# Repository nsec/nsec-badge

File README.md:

NorthSec 2025 badge
===================

Brought to you by the Team badge of NorthSec.

## Overview

<p align="center">
   <br>
</p>

## Hardware

The NorthSec 2025 badge is loosely based on the ESP32-C3 design with an
[ESP32-C3 microcontroller](https://www.espressif.com/en/products/socs/esp32-c3)
(ESP32-C3-WROOM-02-N4) which is used to drive several periphery devices:

- Eighteen [NeoPixel](https://en.wikipedia.org/wiki/Adafruit_Industries#NeoPixel) RGB LEDs
- Five buttons
- One IR 'pairing' connector
- Two [Shitty Add-On V1.69bis](https://hackaday.com/2019/03/20/introducing-the-shitty-add-on-v1-69bis-standard/) connector

The badge is powered through a USB-C port or through 3 AAA batteries.

If you wish to hack your badge or create a new one based on the hardware. All
the information [is available here](hw/2025/).

## Building the firmware

The firmware is based on the [Espressif IoT Development
Framework](https://docs.platformio.org/en/latest/frameworks/espidf.html). The
build system uses
[PlatformIO](https://docs.platformio.org/en/stable/what-is-platformio.html) to
easily manage the dependencies.

You can install it on Debian / Ubuntu in a python virtualenv with these
commands:

```bash
sudo apt install python3-virtualenv

virtualenv .venv
. .venv/bin/activate

pip install platformio
```

The installation procedure for your OS may differ a little, please consult the
[PlatformIO
documentation](https://docs.platformio.org/en/stable/core/installation/index.html)
if you have any difficulties.

Once the installation is complete you can build the firmware:

```bash
# Conference firmware
pio run -e conference

# CTF firmware
pio run -e ctf
```

## Flashing

Flash the firmware with this command:

```bash
# Conference firmware
pio run -t upload -e conference

# CTF firmware
pio run -t upload -e ctf
```

If multiple badges are connected, you can select which badge will be flash with
the `--upload-port <port_name>` option:

```bash
# Conference firmware
pio run -t upload -e conference --upload-port <port_name>
```

To improve the upload speed, you can skip the build validation/process with the
`-t nobuild` option:

```bash
# Conference firmware
pio run -t upload -t nobuild -e conference
```

## Debugging

To read the logging statements output on the USB serial interface, it is
possible to use `pio device monitor` or `idf.py`'s `monitor` command.

However, you can use your preferred terminal emulator by pointing it to the
`/dev/ttyACM0` device. The badge is configured to output at `115200` bauds,
without parity, and with one stop bit per character.

Note that electrically resetting the board using the hardware switch will cause
the pseudo-terminal device to disappear, making it hard to read the logs
emitted during boot.

Pulsing the DTR signal (lowering it for 1 second) will cause the board to reset
without affecting the pseudo-terminal device, allowing you to read early-boot
messages. This is supported by most terminal emulators.

## Credits
NorthSec CTF badge 2025 is brought to you by the teamwork of:

 - [abdelq](https://github.com/abdelq)
 - [IterateMe](https://github.com/IterateMe)
 - [lle](https://github.com/lle)
 - [nyx0](https://github.com/nyx0)
 - [p0ns](https://github.com/p0ns)
 - [padraignix](https://github.com/padraignix)
 - [Svieg](https://github.com/Svieg)
 - [sylemieux](https://github.com/sylemieux)
 - [TheKGBSpy](https://github.com/TheKGBSpy)
 - [mjeanson](https://github.com/mjeanson)

Special thanks to:
 - [20th](https://github.com/20th)
 - [jgalar](https://github.com/jgalar)

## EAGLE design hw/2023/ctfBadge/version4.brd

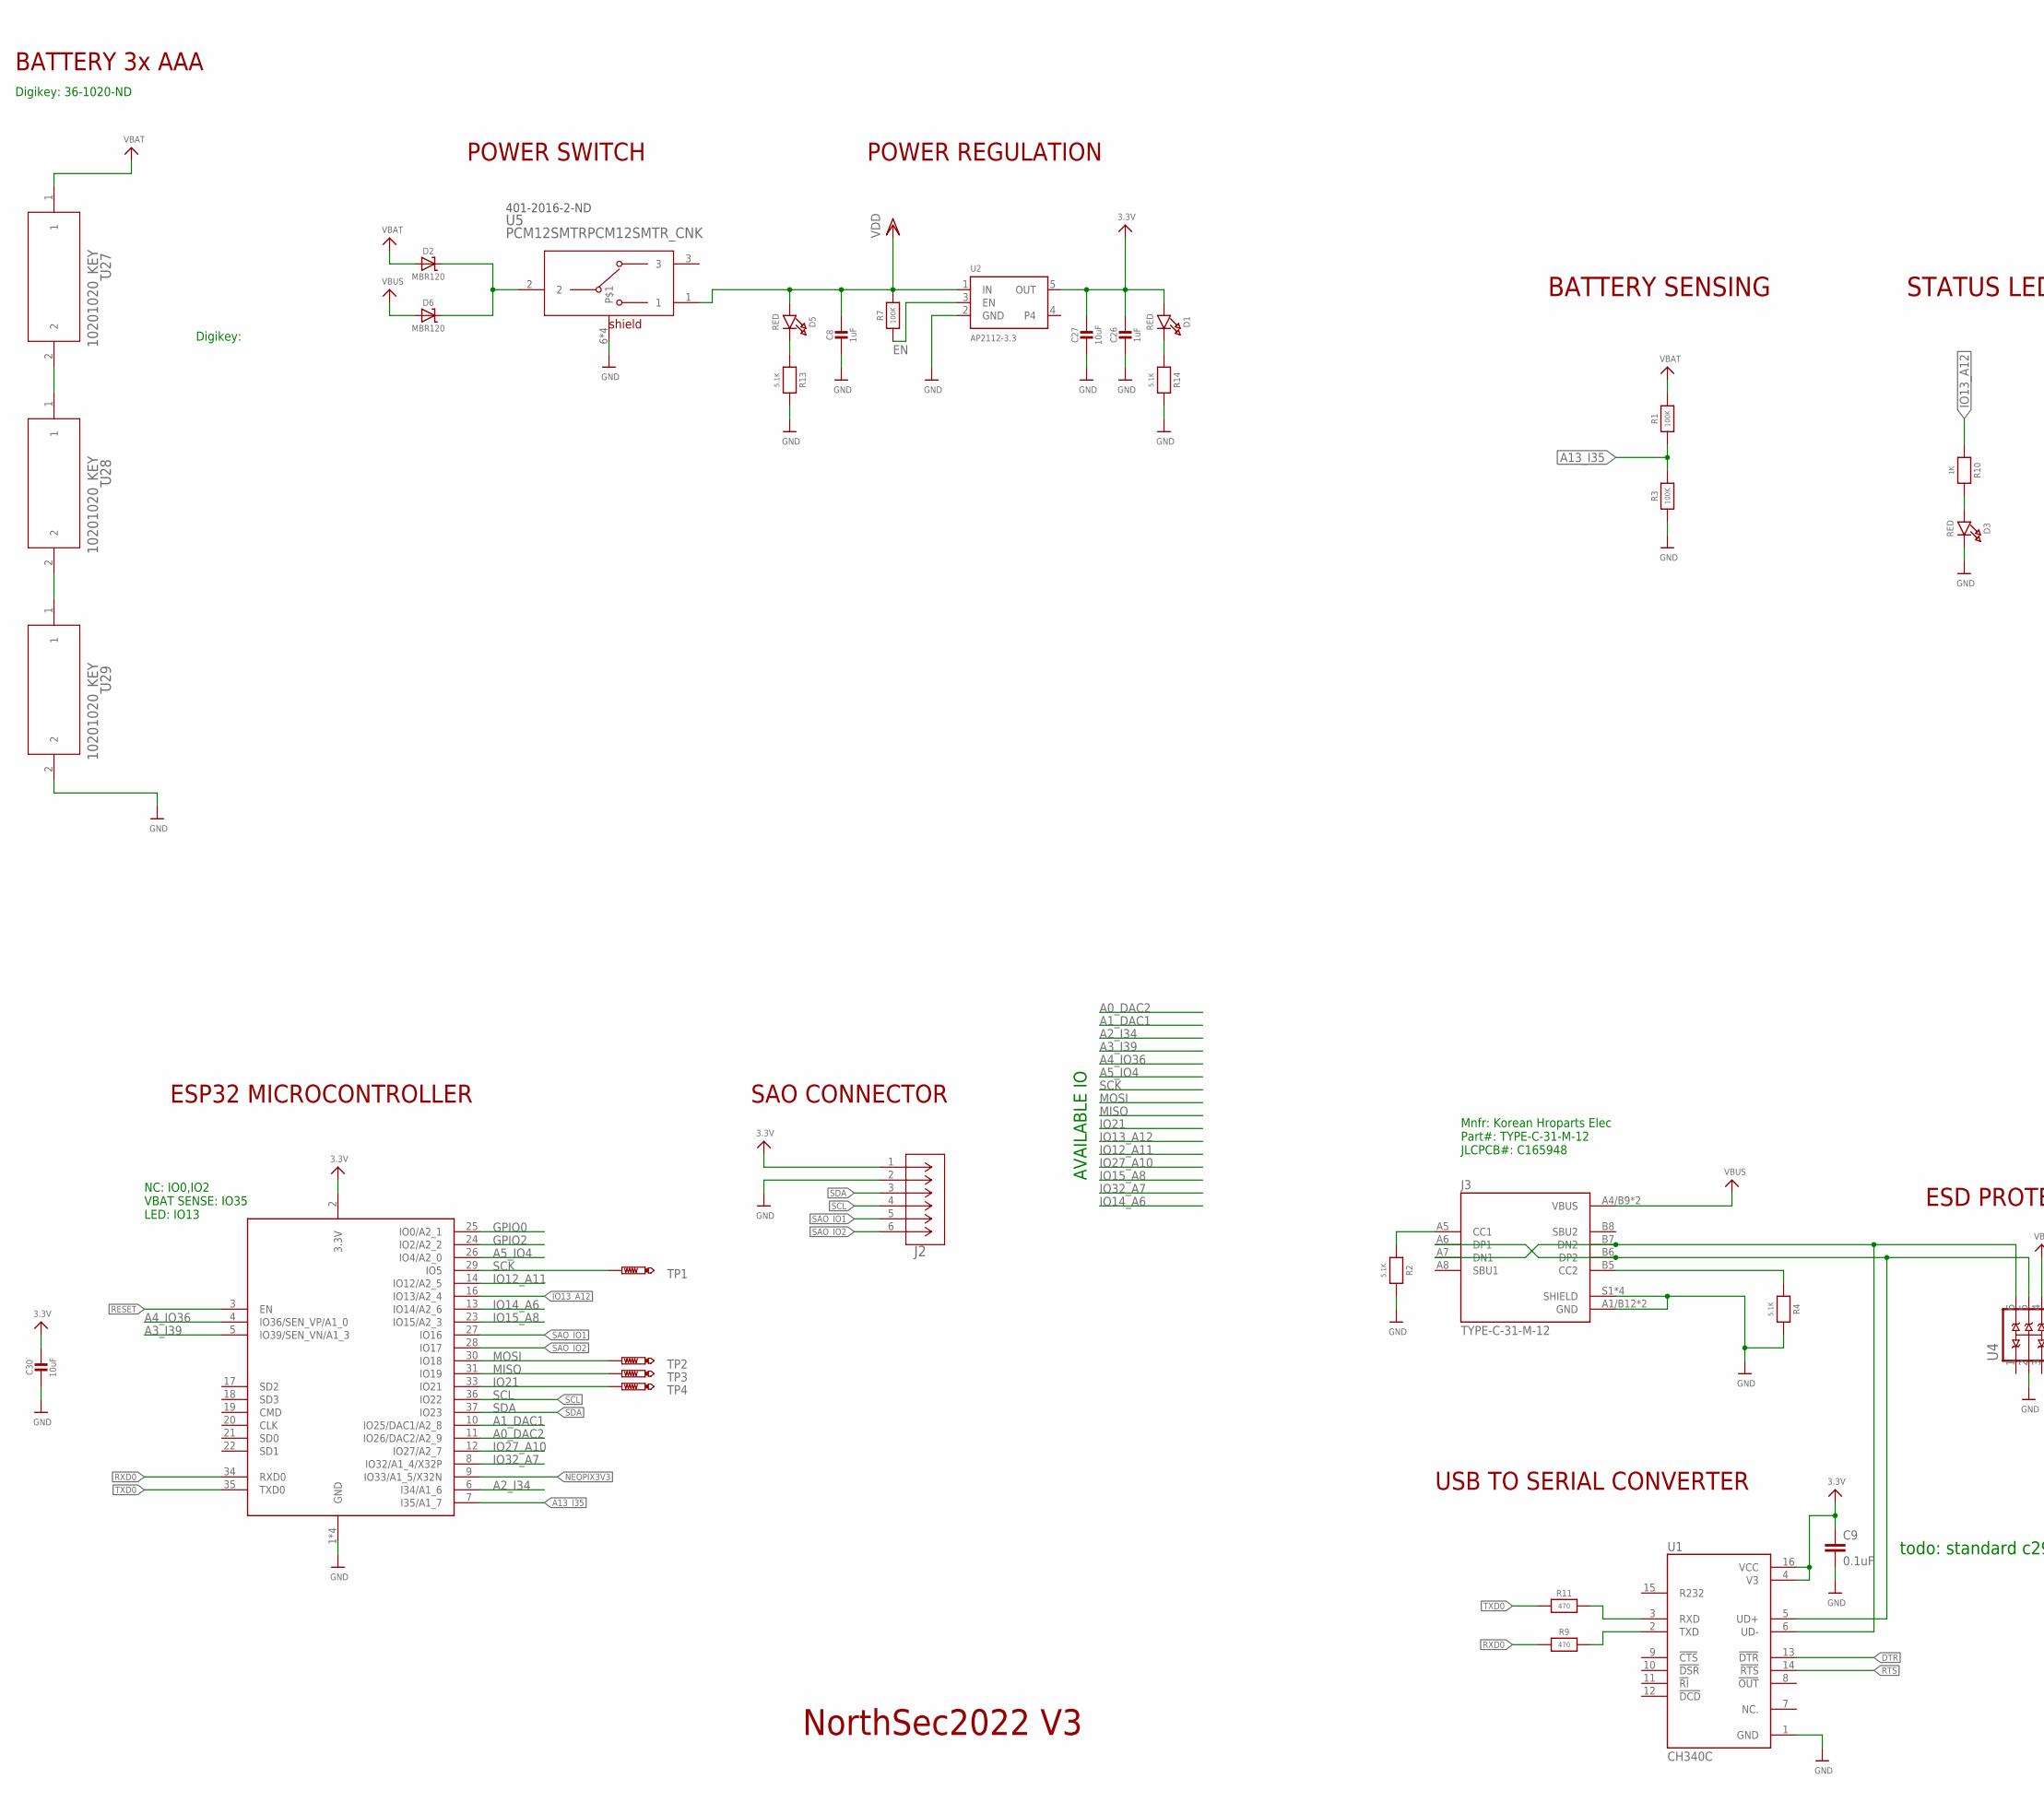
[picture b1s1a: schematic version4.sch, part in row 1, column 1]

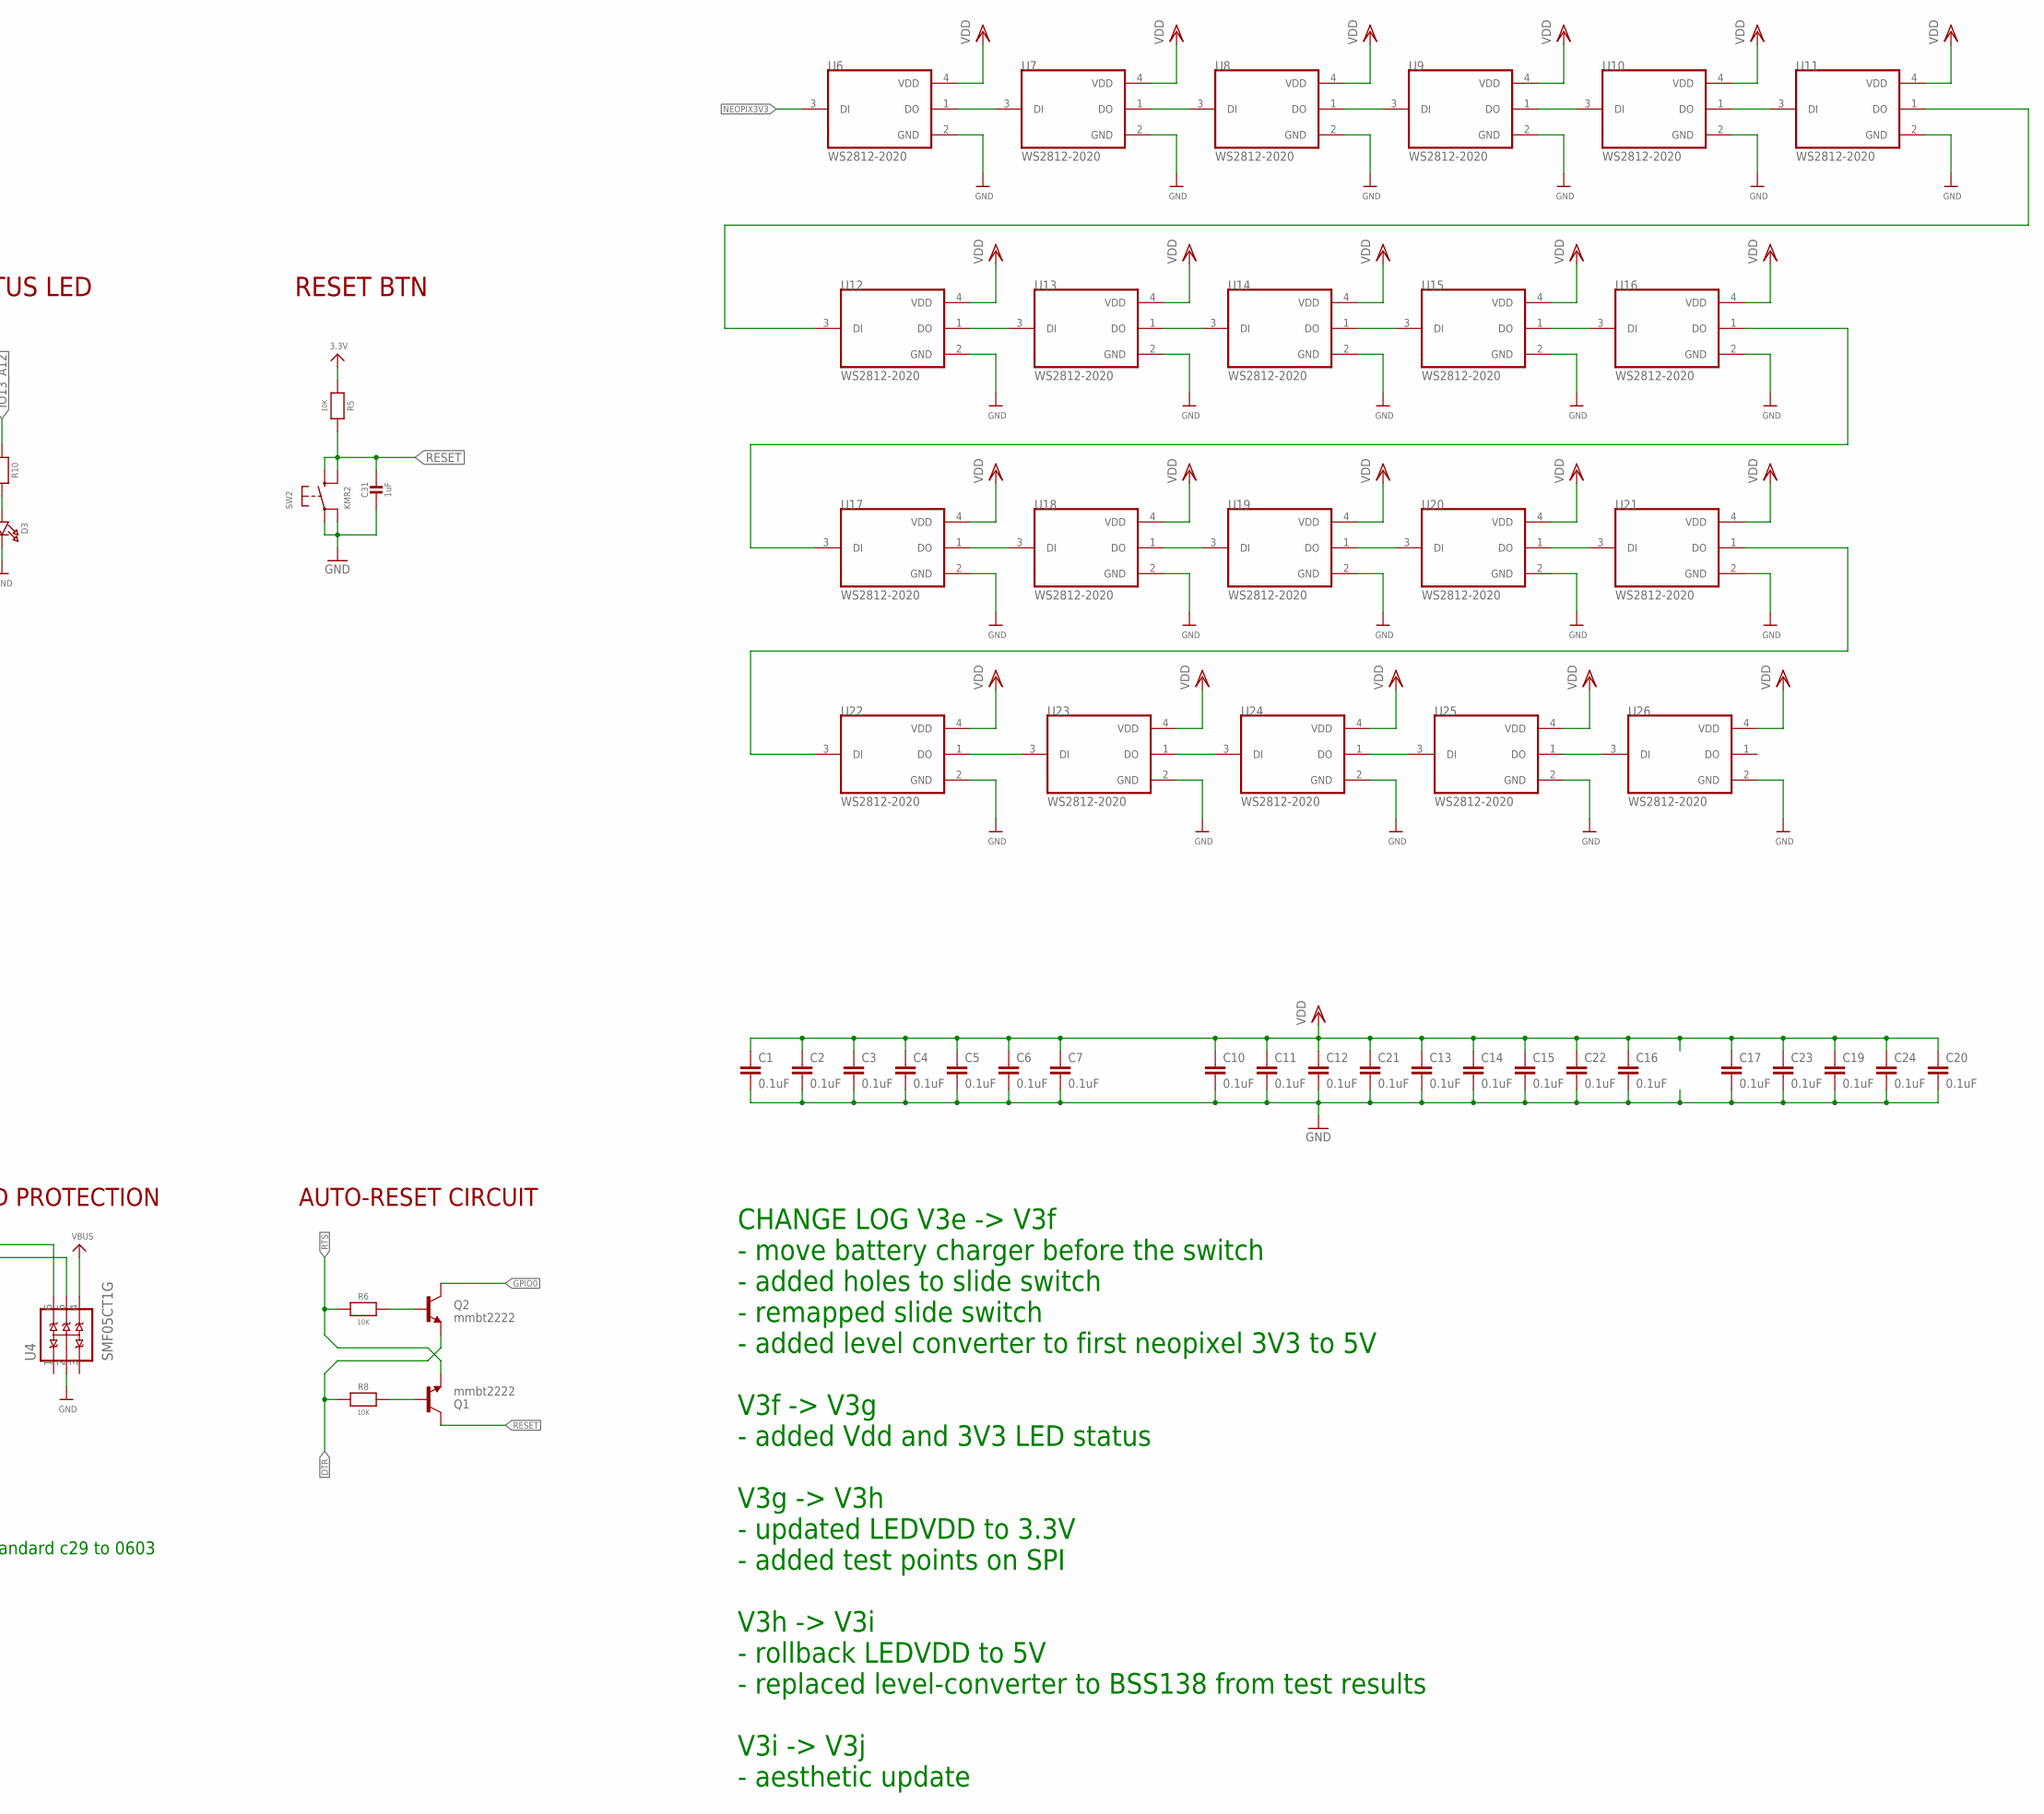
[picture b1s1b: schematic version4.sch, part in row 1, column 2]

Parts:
C1, C2, C3, C4, C5, C6, C7, C9, C10, C11, C12, C13, C14, C15, C16, C17, C19, C20, C21, C22, C23, C24: 0.1uF; C0603
C8, C26, C31: 1uF; 0603-NO
C27, C30: 10uF; 0805-NO
D1, D3, D5: RED; CHIPLED_0805_NOOUTLINE
D2, D6: MBR120; SOD-123
J2: SSW-103-22-F-D-VS-K-TRCON3_SSW-D-DUMZ_HDR_SAI; CON3_SSW-D-DUMZ_HDR_SAI
J3: TYPE-C-31-M-12; HRO_TYPE-C-31-M-12
Q1, Q2: mmbt2222; SOT23-3
R1, R3, R7: 100K; 0603-NO
R2, R4, R13, R14: 5.1K; 0603-NO
R5, R6, R8: 10K; 0603-NO
R9, R11: 470; 0603-NO
R10: 1K; 0603-NO
SW2: KMR2; BTN_KMR2_4.6X2.8
TP1, TP2, TP3, TP4: PTR1B1,27; B1,27
U1: CH340C; SOIC127P600X180-16N
U2: AP2112-3.3; SOT23-5
U4: SMF05CT1G; SOT65P210X110-6N
U5: PCM12SMTRPCM12SMTR_CNK; PCM12SMTR_CNK
U6, U7, U8, U9, U10, U11, U12, U13, U14, U15, U16, U17, U18, U19, U20, U21, U22, U23, U24, U25, U26: WS2812-2020; LED_WS2812-2020
U27, U28, U29: 10201020_KEY; 1020_KEY
X2: ESP32_WROOM32_SKINNY; WROOM32_SKINNY

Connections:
3.3V: C9.1, C26.1, C27.1, C30.1, D1.A, J2.1, R5.1, U1.4 (V3), U1.16 (VCC), U2.5 (OUT), X2.2 (3.3V)
A0_DAC2: X2.11 (IO26/DAC2/A2_9)
A1_DAC1: X2.10 (IO25/DAC1/A2_8)
A2_I34: X2.6 (I34/A1_6)
A3_I39: X2.5 (IO39/SEN_VN/A1_3)
A4_IO36: X2.4 (IO36/SEN_VP/A1_0)
A5_IO4: X2.26 (IO4/A2_0)
A13_I35: R1.1, R3.2, X2.7 (I35/A1_7)
DTR: Q2.2 (E), R8.1, U1.13 (!DTR)
EN: R7.1, U2.3 (EN)
GND: C1.2, C2.2, C3.2, C4.2, C5.2, C6.2, C7.2, C8.2, C9.2, C10.2, C11.2, C12.2, C13.2, C14.2, C15.2, C16.2, C17.2, C19.2, C20.2, C21.2, C22.2, C23.2, C24.2, C26.2, C27.2, C30.2, C31.2, D3.C, J2.2, J3.A1/B12 (GND), J3.B1/A12 (GND), J3.S1 (SHIELD), J3.S2 (SHIELD), J3.S3 (SHIELD), J3.S4 (SHIELD), R2.2, R3.1, R4.2, R13.2, R14.2, SW2.A, SW2.A' (P1), U1.1 (GND), U2.2 (GND), U4.2 (A), U5.6, U5.7, U5.8, U5.9, U6.2 (GND), U7.2 (GND), U8.2 (GND), U9.2 (GND), U10.2 (GND), U11.2 (GND), U12.2 (GND), U13.2 (GND), U14.2 (GND), U15.2 (GND), U16.2 (GND), U17.2 (GND), U18.2 (GND), U19.2 (GND), U20.2 (GND), U21.2 (GND), U22.2 (GND), U23.2 (GND), U24.2 (GND), U25.2 (GND), U26.2 (GND), U29.2, X2.1 (GND), X2.15 (GND), X2.38 (GND), X2.P$1 (GND)
GPIO0: Q2.3 (C), X2.25 (IO0/A2_1)
GPIO2: X2.24 (IO2/A2_2)
IO12_A11: X2.14 (IO12/A2_5)
IO13_A12: R10.1, X2.16 (IO13/A2_4)
IO14_A6: X2.13 (IO14/A2_6)
IO15_A8: X2.23 (IO15/A2_3)
IO21: TP4.TP, X2.33 (IO21)
IO27_A10: X2.12 (IO27/A2_7)
IO32_A7: X2.8 (IO32/A1_4/X32P)
MISO: TP3.TP, X2.31 (IO19)
MOSI: TP2.TP, X2.30 (IO18)
unnamed: U7.1 (DO), U8.3 (DI)
unnamed: U8.1 (DO), U9.3 (DI)
unnamed: U23.1 (DO), U24.3 (DI)
unnamed: U24.1 (DO), U25.3 (DI)
unnamed: U25.1 (DO), U26.3 (DI)
unnamed: J3.B5 (CC2), R4.1
unnamed: D2.C, D6.C, U5.2
unnamed: J3.A5 (CC1), R2.1
unnamed: U22.1 (DO), U23.3 (DI)
unnamed: U28.2, U29.1
unnamed: U27.2, U28.1
unnamed: R9.2, U1.2 (TXD)
unnamed: J3.A6 (DP1), J3.B6 (DP2), U1.5 (UD+), U4.5 (C4)
unnamed: J3.A7 (DN1), J3.B7 (DN2), U1.6 (UD-), U4.6 (C5)
unnamed: Q1.1 (B), R8.2
unnamed: Q2.1 (B), R6.2
unnamed: R11.2, U1.3 (RXD)
unnamed: D3.A, R10.2
unnamed: D5.C, R13.1
unnamed: D1.C, R14.1
unnamed: U6.1 (DO), U7.3 (DI)
unnamed: U9.1 (DO), U10.3 (DI)
unnamed: U10.1 (DO), U11.3 (DI)
unnamed: U11.1 (DO), U12.3 (DI)
unnamed: U12.1 (DO), U13.3 (DI)
unnamed: U13.1 (DO), U14.3 (DI)
unnamed: U14.1 (DO), U15.3 (DI)
unnamed: U15.1 (DO), U16.3 (DI)
unnamed: U16.1 (DO), U17.3 (DI)
unnamed: U17.1 (DO), U18.3 (DI)
unnamed: U18.1 (DO), U19.3 (DI)
unnamed: U19.1 (DO), U20.3 (DI)
unnamed: U20.1 (DO), U21.3 (DI)
unnamed: U21.1 (DO), U22.3 (DI)
NEOPIX3V3: U6.3 (DI), X2.9 (IO33/A1_5/X32N)
RESET: C31.1, Q1.3 (C), R5.2, SW2.B (S), SW2.B' (S1), X2.3 (EN)
RTS: Q1.2 (E), R6.1, U1.14 (!RTS)
RXD0: R9.1, X2.34 (RXD0)
SAO_IO1: J2.5, X2.27 (IO16)
SAO_IO2: J2.6, X2.28 (IO17)
SCK: TP1.TP, X2.29 (IO5)
SCL: J2.4, X2.36 (IO22)
SDA: J2.3, X2.37 (IO23)
TXD0: R11.1, X2.35 (TXD0)
VBAT: D2.A, R1.2, U27.1
VBUS: D6.A, J3.A4/B9 (VBUS), J3.B4/A9 (VBUS), U4.4 (C3)
VDD: C1.1, C2.1, C3.1, C4.1, C5.1, C6.1, C7.1, C8.1, C10.1, C11.1, C12.1, C13.1, C14.1, C15.1, C16.1, C17.1, C19.1, C20.1, C21.1, C22.1, C23.1, C24.1, D5.A, R7.2, U2.1 (IN), U5.1, U6.4 (VDD), U7.4 (VDD), U8.4 (VDD), U9.4 (VDD), U10.4 (VDD), U11.4 (VDD), U12.4 (VDD), U13.4 (VDD), U14.4 (VDD), U15.4 (VDD), U16.4 (VDD), U17.4 (VDD), U18.4 (VDD), U19.4 (VDD), U20.4 (VDD), U21.4 (VDD), U22.4 (VDD), U23.4 (VDD), U24.4 (VDD), U25.4 (VDD), U26.4 (VDD)

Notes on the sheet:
POWER REGULATION
RESET BTN
USB TO SERIAL CONVERTER
ESP32 MICROCONTROLLER
NC: IO0,IO2 VBAT SENSE: IO35 LED: IO13
BATTERY SENSING
STATUS LED
ESD PROTECTION
AUTO-RESET CIRCUIT
AVAILABLE IO
401-2016-2-ND
CHANGE LOG V3e -> V3f - move battery charger before the switch - added holes to slide switch - remapped slide switch - added level converter to first neopixel 3V3 to 5V V3f -> V3g - added Vdd and 3V3 LED status V3g -> V3h - updated LEDVDD to 3.3V - added test points on SPI V3h -> V3i - rollback LED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
POWER SWITCH
SAO CONNECTOR
NorthSec2022 V3
BATTERY 3x AAA
Mnfr: Korean Hroparts Elec Part#: TYPE-C-31-M-12 JLCPCB#: C165948
Digikey:
Digikey: 36-1020-ND
todo: standard c29 to 0603

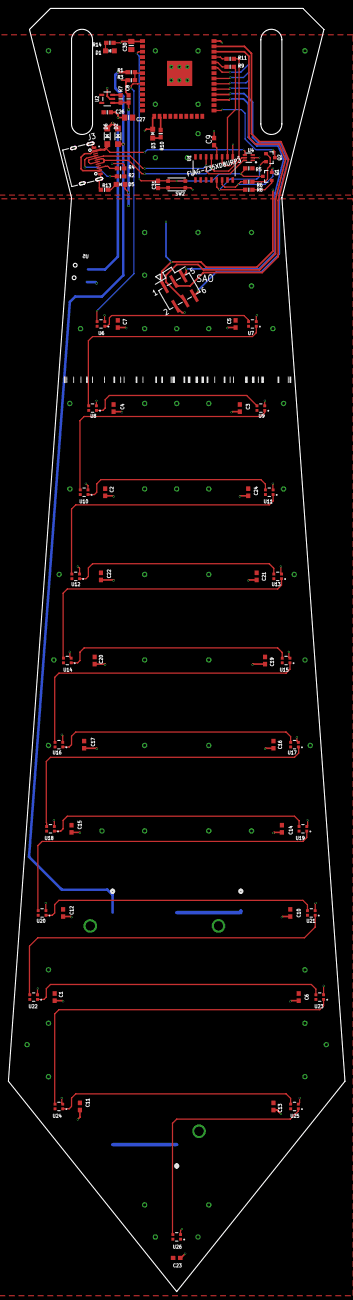
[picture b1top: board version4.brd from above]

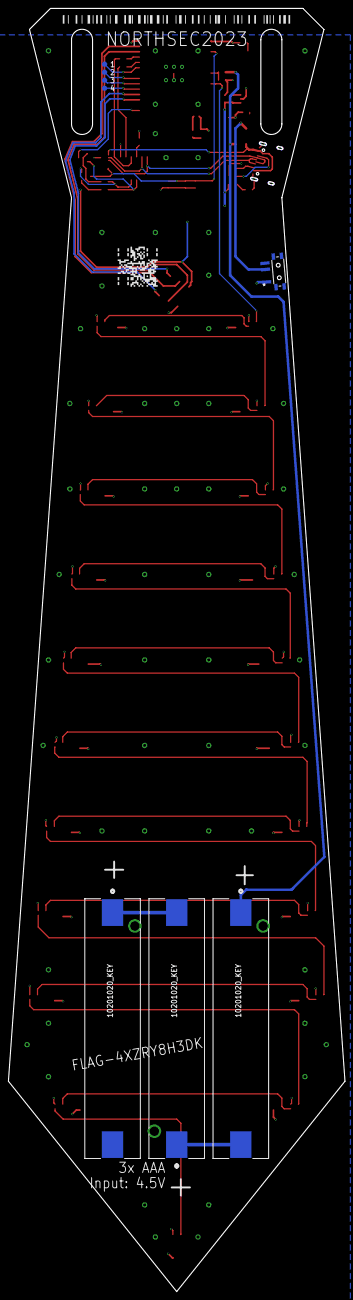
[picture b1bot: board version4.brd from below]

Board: 2 copper layers, 80.0 x 305.0 mm, 83 parts (8 on the bottom side), 57 nets.

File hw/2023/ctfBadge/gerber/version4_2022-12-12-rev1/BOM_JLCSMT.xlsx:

Comment | Designator | Footprint | JLCPCB Part #（optional）
0.1uF | C1, C2, C3, C4, C5, C6, C7, C9, C10, C11, C12, C13, C14, C15, C16, C17, C19, C2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 | C0603 | C14663
100K | R1, R3, R7 | 0603-NO | C25803
10201020_KEY | U27, U28, U29 | 1020_KEY
10K | R5, R6, R8 | 0603-NO | C25804
10uF | C27, C30 | 0805-NO | C440198
1K | R10 | 0603-NO | C21190
1uF | C8, C26, C31 | 0603-NO | C15849
470 | R9, R11 | 0603-NO | C114669
5.1K | R2, R4, R13, R14 | 0603-NO | C23186
AP2112-3.3 | U2 | SOT23-5 | C150742
CH340C | U1 | SOIC127P600X180-16N | C84681
ESP32_WROOM32_SKINNY | X2 | WROOM32_SKINNY | C82899
KMR2 | SW2 | BTN_KMR2_4.6X2.8 | C72443 | Or C269272
MBR120 | D2, D6 | SOD-123 | C130880
PCM12SMTRPCM12SMTR_CNK | U5 | PCM12SMTR_CNK | 401-2016-2-ND
RED | D1, D3, D5 | CHIPLED_0805_NOOUTLINE | C84256
SMF05CT1G | U4 | SOT65P210X110-6N | C558443
SSW-103-22-F-D-VS-K-TRCON3_SSW-D-DUMZ_HDR_SAI | J2 | CON3_SSW-D-DUMZ_HDR_SAI
TYPE-C-31-M-12 | J3 | HRO_TYPE-C-31-M-12 | C165948
WS2812-2020 | U6, U7, U8, U9, U10, U11, U12, U13, U14, U15, U16, U17, U18, U19, U20, U21, U22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 | LED_WS2812-2020 | C965555
mmbt2222 | Q1, Q2 | SOT23-3 | C8512

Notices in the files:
parts and their libraries:
microbuilder: This work is placed in the public domain, and may be freely used for commercial and non-commercial work with the following conditions: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
SparkFun-Switches: Licensing: Creative Commons ShareAlike 4.0 International - https://creativecommons.org/licenses/by-sa/4.0
